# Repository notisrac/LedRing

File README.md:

# LED ring

A small ring with 6 leds on it. Outer diameter = 25mm, inner diameter = 9.5mm.

The ring shaped PCB was created with [OpenSCAD](http://www.openscad.org/), saved in .dfx, then converted to .scr with [Micromagic System's DXF2SCR converter](http://www.micromagicsystems.com/#/dxf-converter/4523812840).

## Pictures
Schematic:

Assembled:

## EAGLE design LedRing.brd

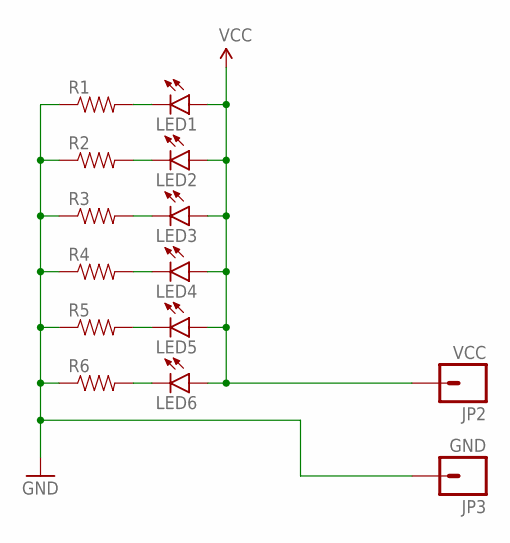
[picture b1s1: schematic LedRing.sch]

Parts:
JP2: VCC; 1X01NS-KIT
JP3: GND; 1X01NS-KIT
LED1, LED2, LED3, LED4, LED5, LED6: LED1206; LED-1206
R1, R2, R3, R4, R5, R6: RESISTOR1206; 1206

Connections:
GND: JP3.1, R1.1, R2.1, R3.1, R4.1, R5.1, R6.1
unnamed: LED1.C, R1.2
unnamed: LED2.C, R2.2
unnamed: LED3.C, R3.2
unnamed: LED4.C, R4.2
unnamed: LED5.C, R5.2
unnamed: LED6.C, R6.2
VCC: JP2.1, LED1.A, LED2.A, LED3.A, LED4.A, LED5.A, LED6.A

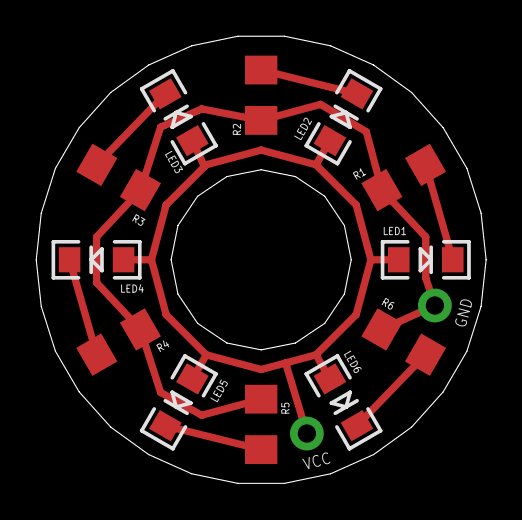
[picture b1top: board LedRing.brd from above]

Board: 2 copper layers, 25.0 x 24.8 mm, 14 parts (0 on the bottom side), 8 nets.

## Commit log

2018-07-27 Fixed README issues
2018-07-28 Added GA beacon to the README
2018-07-29 Removed epf file

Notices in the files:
parts and their libraries:
SparkFun-LED: Licensing: Creative Commons ShareAlike 4.0 International - https://creativecommons.org/licenses/by-sa/4.0
